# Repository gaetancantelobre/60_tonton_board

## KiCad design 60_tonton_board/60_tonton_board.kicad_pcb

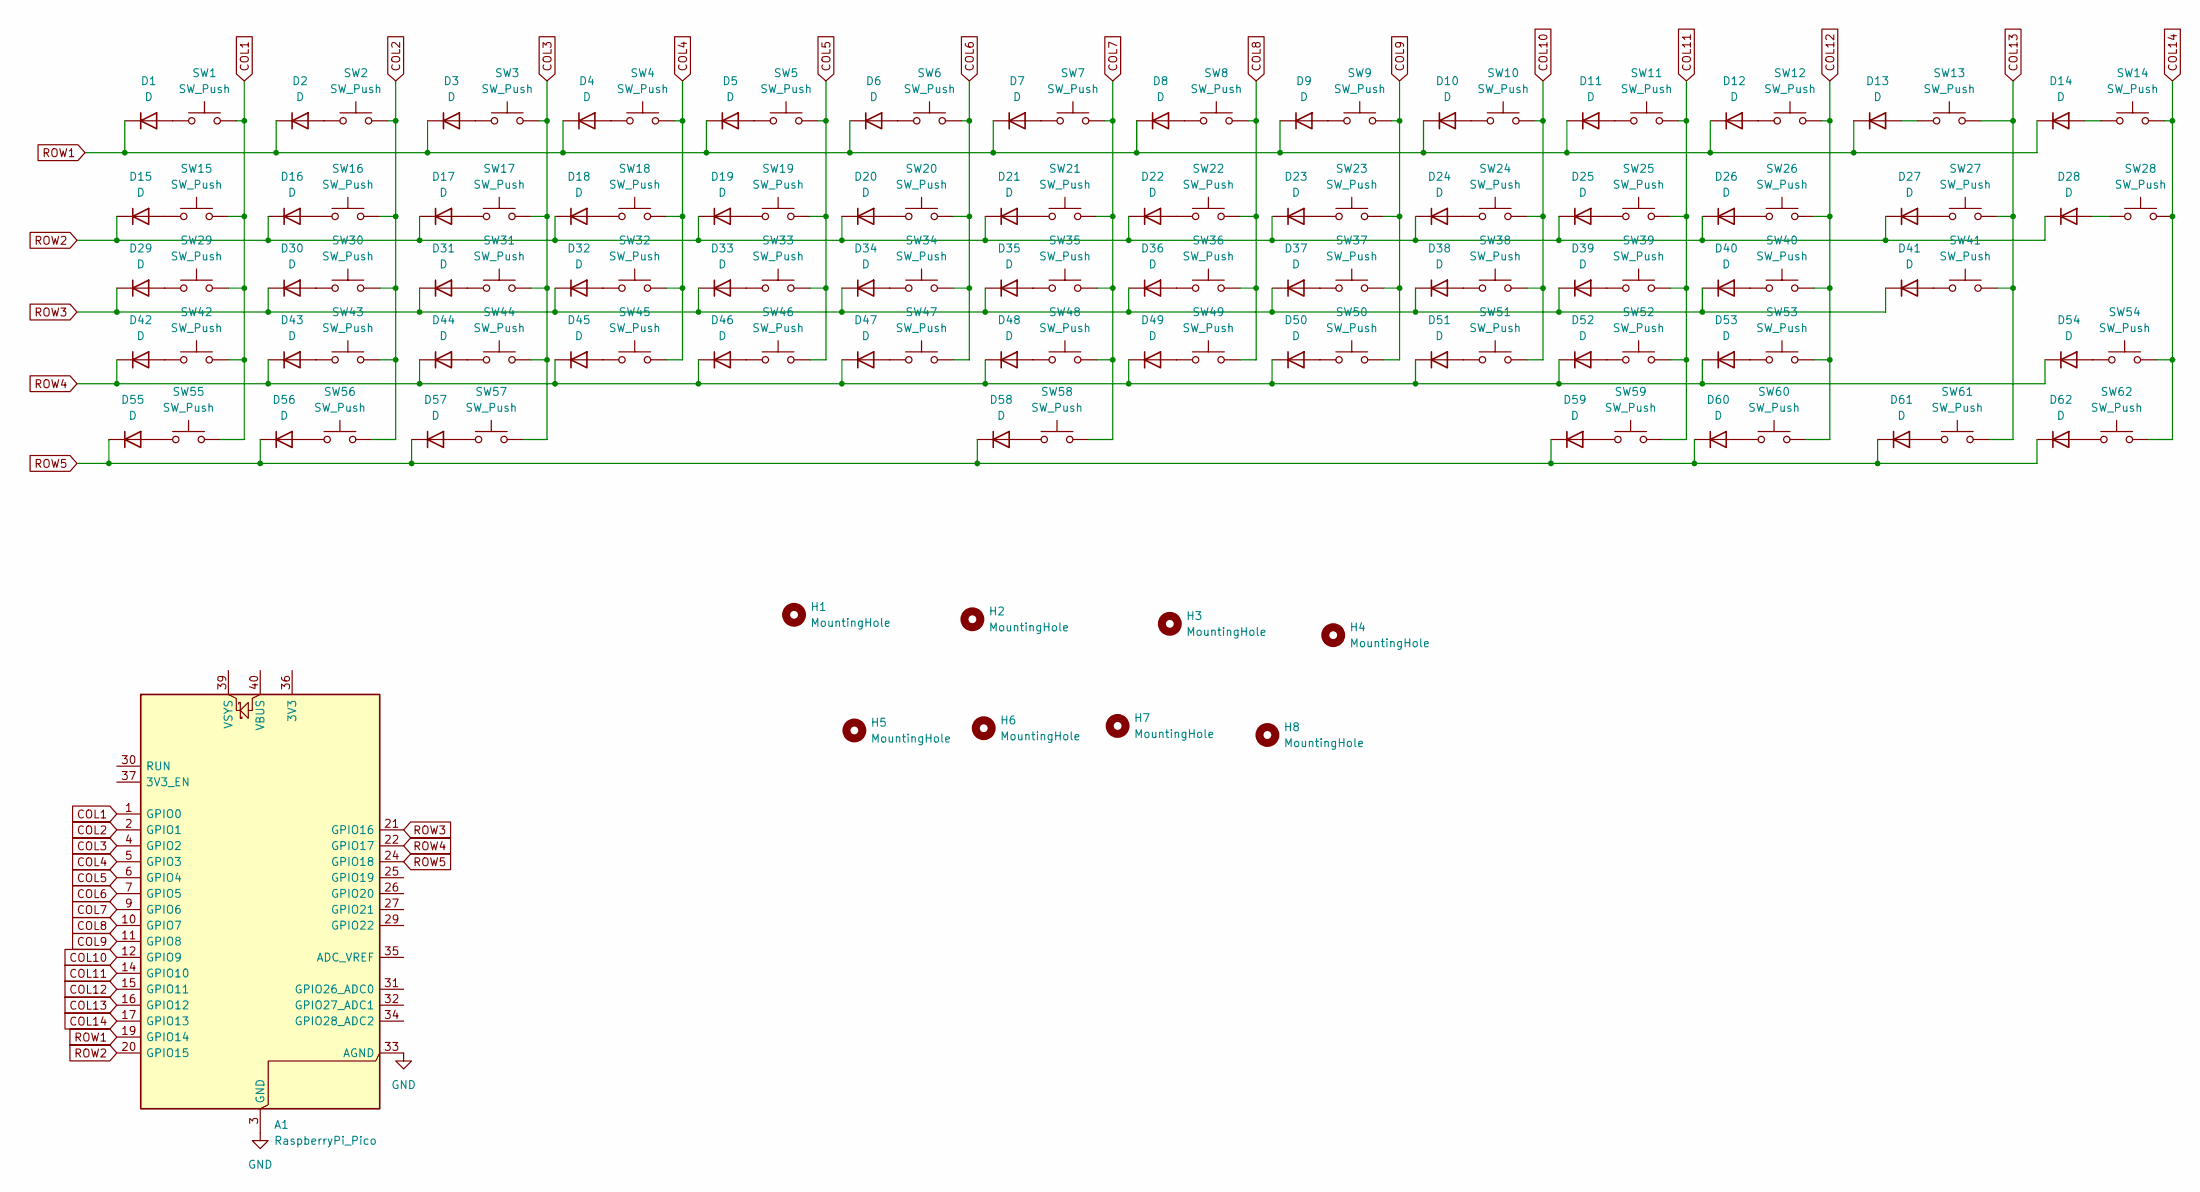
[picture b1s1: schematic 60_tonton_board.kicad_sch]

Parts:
A1: RaspberryPi_Pico; RaspberryPi_Pico_Common_Unspecified
D1, D2, D3, D4, D5, D6, D7, D8, D9, D10, D11, D12, D13, D14, D15, D16, D17, D18, D19, D20, D21, D22, D23, D24, D25, D26, D27, D28, D29, D30, D31, D32, D33, D34, D35, D36, D37, D38, D39, D40, D41, D42, D43, D44, D45, D46, D47, D48, D49, D50, D51, D52, D53, D54, D55, D56, D57, D58, D59, D60, D61, D62: D; D_SOD-123
H1, H2, H3, H4, H5, H6, H7, H8: MountingHole; MountingHole_3mm
SW1, SW2, SW3, SW4, SW5, SW6, SW7, SW8, SW9, SW10, SW11, SW12, SW13, SW16, SW17, SW18, SW19, SW20, SW21, SW22, SW23, SW24, SW25, SW26, SW27, SW30, SW31, SW32, SW33, SW34, SW35, SW36, SW37, SW38, SW39, SW40, SW41, SW43, SW44, SW45, SW46, SW47, SW48, SW49, SW50, SW51, SW52, SW53: SW_Push; SW_Cherry_MX_1.00u_PCB
SW14: SW_Push; SW_Cherry_MX_2.00u_PCB
SW15: SW_Push; SW_Cherry_MX_1.50u_PCB
SW28: SW_Push; SW_Cherry_MX_ISOEnter_PCB
SW29: SW_Push; SW_Cherry_MX_1.75u_PCB
SW42, SW55, SW56, SW57, SW59, SW60, SW61, SW62: SW_Push; SW_Cherry_MX_1.25u_PCB
SW54: SW_Push; SW_Cherry_MX_2.75u_PCB
SW58: SW_Push; SW_Cherry_MX_6.25u_PCB

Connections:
COL1: A1.1 (GPIO0), SW1.2, SW15.2, SW29.2, SW42.2, SW55.2
COL2: A1.2 (GPIO1), SW2.2, SW16.2, SW30.2, SW43.2, SW56.2
COL3: A1.4 (GPIO2), SW3.2, SW17.2, SW31.2, SW44.2, SW57.2
COL4: A1.5 (GPIO3), SW4.2, SW18.2, SW32.2, SW45.2
COL5: A1.6 (GPIO4), SW5.2, SW19.2, SW33.2, SW46.2
COL6: A1.7 (GPIO5), SW6.2, SW20.2, SW34.2, SW47.2
COL7: A1.9 (GPIO6), SW7.2, SW21.2, SW35.2, SW48.2, SW58.2
COL8: A1.10 (GPIO7), SW8.2, SW22.2, SW36.2, SW49.2
COL9: A1.11 (GPIO8), SW9.2, SW23.2, SW37.2, SW50.2
COL10: A1.12 (GPIO9), SW10.2, SW24.2, SW38.2, SW51.2
COL11: A1.14 (GPIO10), SW11.2, SW25.2, SW39.2, SW52.2, SW59.2
COL12: A1.15 (GPIO11), SW12.2, SW26.2, SW40.2, SW53.2, SW60.2
COL13: A1.16 (GPIO12), SW13.2, SW27.2, SW41.2, SW61.2
COL14: A1.17 (GPIO13), SW14.2, SW28.2, SW54.2, SW62.2
GND: A1.3 (GND), A1.8 (GND), A1.13 (GND), A1.18 (GND), A1.23 (GND), A1.28 (GND), A1.33 (AGND), A1.38 (GND)
unnamed: D1.2 (A), SW1.1
unnamed: D2.2 (A), SW2.1
unnamed: D3.2 (A), SW3.1
unnamed: D4.2 (A), SW4.1
unnamed: D5.2 (A), SW5.1
unnamed: D6.2 (A), SW6.1
unnamed: D7.2 (A), SW7.1
unnamed: D8.2 (A), SW8.1
unnamed: D9.2 (A), SW9.1
unnamed: D10.2 (A), SW10.1
unnamed: D11.2 (A), SW11.1
unnamed: D12.2 (A), SW12.1
unnamed: D13.2 (A), SW13.1
unnamed: D14.2 (A), SW14.1
unnamed: D15.2 (A), SW15.1
unnamed: D16.2 (A), SW16.1
unnamed: D17.2 (A), SW17.1
unnamed: D18.2 (A), SW18.1
unnamed: D19.2 (A), SW19.1
unnamed: D20.2 (A), SW20.1
unnamed: D21.2 (A), SW21.1
unnamed: D22.2 (A), SW22.1
unnamed: D23.2 (A), SW23.1
unnamed: D24.2 (A), SW24.1
unnamed: D25.2 (A), SW25.1
unnamed: D26.2 (A), SW26.1
unnamed: D27.2 (A), SW27.1
unnamed: D28.2 (A), SW28.1
unnamed: D29.2 (A), SW29.1
unnamed: D30.2 (A), SW30.1
unnamed: D31.2 (A), SW31.1
unnamed: D32.2 (A), SW32.1
unnamed: D33.2 (A), SW33.1
unnamed: D34.2 (A), SW34.1
unnamed: D35.2 (A), SW35.1
unnamed: D36.2 (A), SW36.1
unnamed: D37.2 (A), SW37.1
unnamed: D38.2 (A), SW38.1
unnamed: D39.2 (A), SW39.1
unnamed: D40.2 (A), SW40.1
unnamed: D41.2 (A), SW41.1
unnamed: D42.2 (A), SW42.1
unnamed: D43.2 (A), SW43.1
unnamed: D44.2 (A), SW44.1
unnamed: D45.2 (A), SW45.1
unnamed: D46.2 (A), SW46.1
unnamed: D47.2 (A), SW47.1
unnamed: D48.2 (A), SW48.1
unnamed: D49.2 (A), SW49.1
unnamed: D50.2 (A), SW50.1
unnamed: D51.2 (A), SW51.1
unnamed: D52.2 (A), SW52.1
unnamed: D53.2 (A), SW53.1
unnamed: D54.2 (A), SW54.1
unnamed: D55.2 (A), SW55.1
unnamed: D56.2 (A), SW56.1
unnamed: D57.2 (A), SW57.1
unnamed: D58.2 (A), SW58.1
unnamed: D59.2 (A), SW59.1
unnamed: D60.2 (A), SW60.1
unnamed: D61.2 (A), SW61.1
unnamed: D62.2 (A), SW62.1
ROW1: A1.19 (GPIO14), D1.1 (K), D2.1 (K), D3.1 (K), D4.1 (K), D5.1 (K), D6.1 (K), D7.1 (K), D8.1 (K), D9.1 (K), D10.1 (K), D11.1 (K), D12.1 (K), D13.1 (K), D14.1 (K)
ROW2: A1.20 (GPIO15), D15.1 (K), D16.1 (K), D17.1 (K), D18.1 (K), D19.1 (K), D20.1 (K), D21.1 (K), D22.1 (K), D23.1 (K), D24.1 (K), D25.1 (K), D26.1 (K), D27.1 (K), D28.1 (K)
ROW3: A1.21 (GPIO16), D29.1 (K), D30.1 (K), D31.1 (K), D32.1 (K), D33.1 (K), D34.1 (K), D35.1 (K), D36.1 (K), D37.1 (K), D38.1 (K), D39.1 (K), D40.1 (K), D41.1 (K)
ROW4: A1.22 (GPIO17), D42.1 (K), D43.1 (K), D44.1 (K), D45.1 (K), D46.1 (K), D47.1 (K), D48.1 (K), D49.1 (K), D50.1 (K), D51.1 (K), D52.1 (K), D53.1 (K), D54.1 (K)
ROW5: A1.24 (GPIO18), D55.1 (K), D56.1 (K), D57.1 (K), D58.1 (K), D59.1 (K), D60.1 (K), D61.1 (K), D62.1 (K)

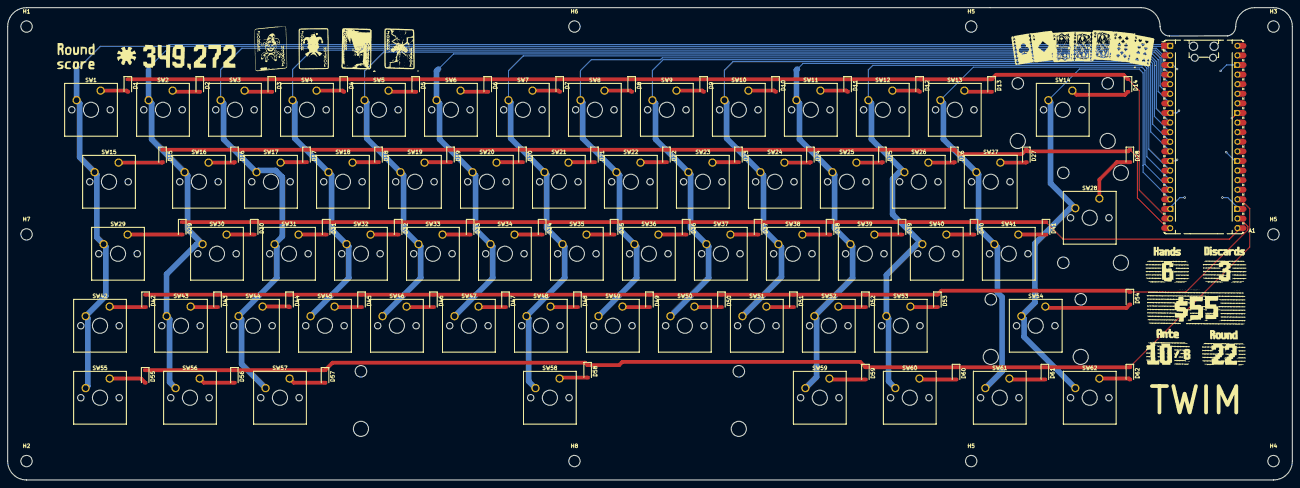
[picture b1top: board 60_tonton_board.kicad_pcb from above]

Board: 2 copper layers, 340.0 x 125.0 mm, 135 parts (0 on the bottom side), 82 nets.

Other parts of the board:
H5#2, H5#3: MountingHole; MountingHole_3mm

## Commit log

2025-05-27 nice
2025-06-14 qzdqzd
2025-06-15 added qmk files to repo
2025-06-21 psuher ca les modos la
2025-12-05 upodated cv
